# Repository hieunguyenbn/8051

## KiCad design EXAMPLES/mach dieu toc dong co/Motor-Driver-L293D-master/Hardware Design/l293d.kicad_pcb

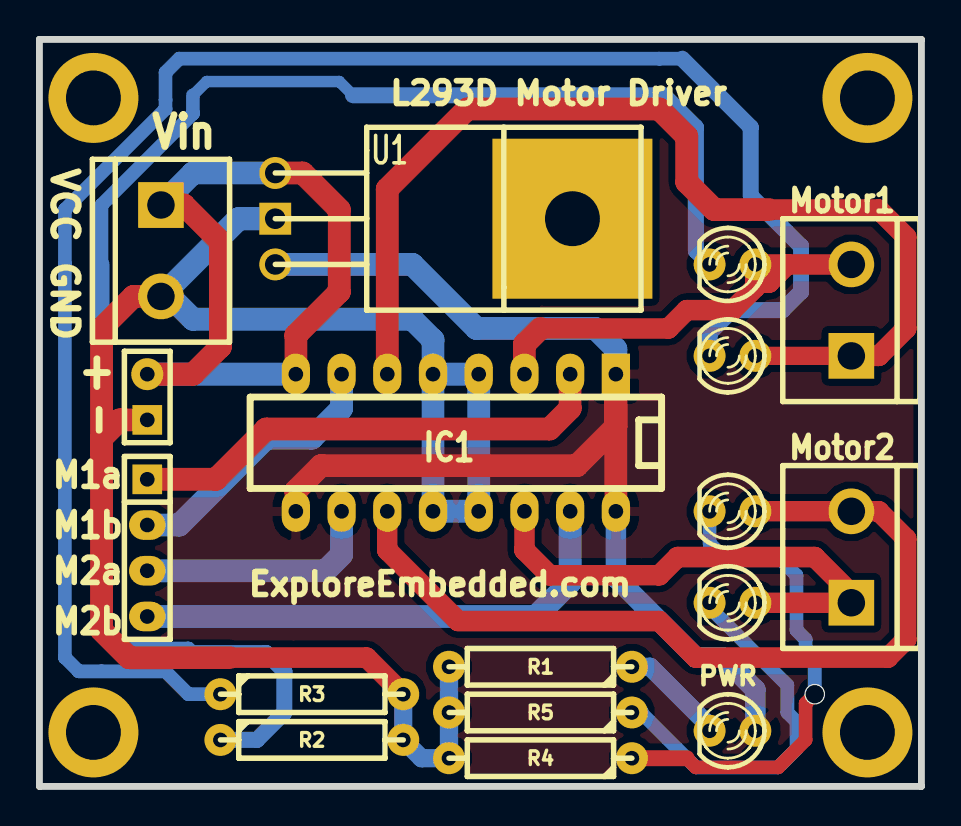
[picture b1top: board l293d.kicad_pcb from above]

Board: 2 copper layers, 49.0 x 41.5 mm, 22 parts (1 on the bottom side), 16 nets.

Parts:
D1, D2, D3, D4, D5: LED; LED-3MM
IC1: L293D; DIP-16__300_ELL
P1: Motar1; bornier2
P2: motar2; bornier2
P3: CONN_4; SIL-4
P4: CONN_2; bornier2
P5, P7, P8, P9: CONN_1; 1pin
P6: CONN_2; SIL-2
R1, R2, R3, R4, R5: 470; R4
U1: LM7805; LM78XX
VAL: REF; Logo_8

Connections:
/+5v: D1.1, IC1.1, IC1.9, IC1.16
/M1a: IC1.2, P3.1
/M1b: IC1.7, P3.2
/M2a: IC1.10, P3.3
/M2b: IC1.15, P3.4
/VCC1: IC1.8, P4.1, P6.2
GND: IC1.4, IC1.5, IC1.12, IC1.13, P4.2, P6.1, R1.2, R2.2, R3.2, R4.2, R5.2
unnamed: D1.2, R1.1
unnamed: D5.2, R5.1
unnamed: D5.1, IC1.14, P2.1
unnamed: D4.2, R4.1
unnamed: D3.2, R3.1
unnamed: D2.2, R2.1
unnamed: D2.1, IC1.3, P1.2
unnamed: D4.1, IC1.11, P2.2
unnamed: D3.1, IC1.6, P1.1

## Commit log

2018-06-09 my CPP projects
2019-02-27 Add documents
2020-03-01 Add example projects
